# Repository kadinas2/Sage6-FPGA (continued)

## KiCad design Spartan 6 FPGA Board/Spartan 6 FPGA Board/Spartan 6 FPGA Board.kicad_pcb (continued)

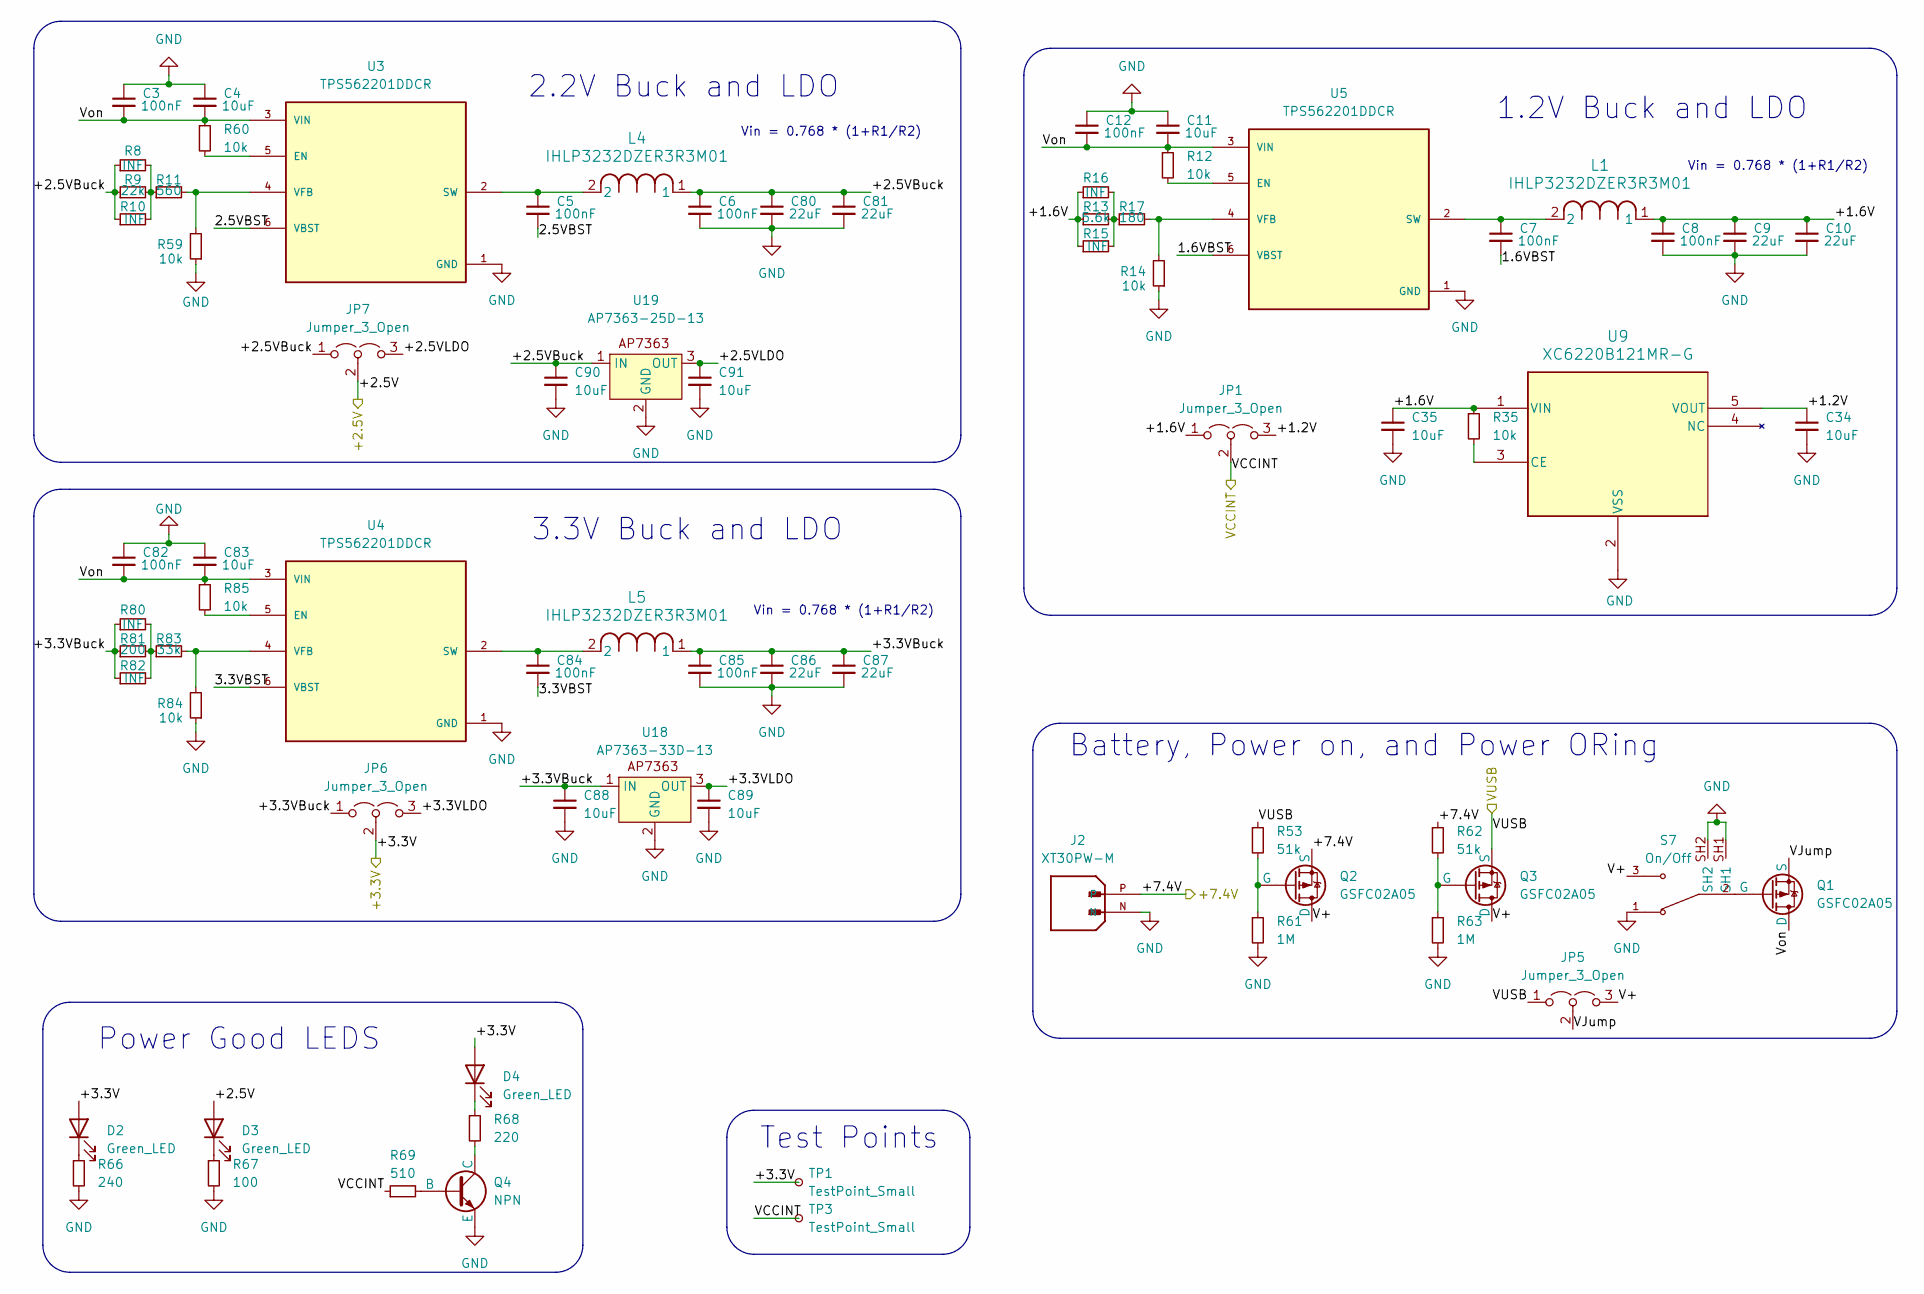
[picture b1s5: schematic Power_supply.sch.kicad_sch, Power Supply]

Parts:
C3, C5, C6, C7, C8, C12, C82, C84, C85: 100nF; C_0805_2012Metric_Pad1.18x1.45mm_HandSolder
C4, C11, C34, C35, C83, C88, C89, C90, C91: 10uF; C_0805_2012Metric_Pad1.18x1.45mm_HandSolder
C9, C10, C80, C81, C86, C87: 22uF; C_0805_2012Metric_Pad1.18x1.45mm_HandSolder
D2, D3, D4: Green_LED; LED_0805_2012Metric
J2: XT30PW-M; AMASS_XT30PW-M; PARTREV 1.2
JP1, JP5, JP6, JP7: Jumper_3_Open; PinHeader_1x03_P2.54mm_Vertical
L1, L4, L5: IHLP3232DZER3R3M01; IND_IHLP-3232DZ_VIS
Q1, Q2, Q3: GSFC02A05; SOT-23
Q4: NPN; SOT-23
R8, R10, R15, R16, R80, R82: INF; R_0805_2012Metric_Pad1.20x1.40mm_HandSolder
R9: 22k; R_0805_2012Metric_Pad1.20x1.40mm_HandSolder
R11: 560; R_0805_2012Metric_Pad1.20x1.40mm_HandSolder
R12, R14, R35, R59, R60, R84, R85: 10k; R_0805_2012Metric_Pad1.20x1.40mm_HandSolder
R13: 5.6k; R_0805_2012Metric_Pad1.20x1.40mm_HandSolder
R17: 180; R_0805_2012Metric_Pad1.20x1.40mm_HandSolder
R53, R62: 51k; R_0805_2012Metric_Pad1.20x1.40mm_HandSolder
R61, R63: 1M; R_0805_2012Metric_Pad1.20x1.40mm_HandSolder
R66: 240; R_0805_2012Metric_Pad1.20x1.40mm_HandSolder
R67: 100; R_0805_2012Metric_Pad1.20x1.40mm_HandSolder
R68: 220; R_0805_2012Metric_Pad1.20x1.40mm_HandSolder
R69: 510; R_0805_2012Metric_Pad1.20x1.40mm_HandSolder
R81: 200; R_0805_2012Metric_Pad1.20x1.40mm_HandSolder
R83: 33k; R_0805_2012Metric_Pad1.20x1.40mm_HandSolder
S7: On/Off; SW_SLW-835636-3A-RA-N-D; PARTREV 1.01
TP1, TP3: TestPoint_Small; TestPoint_Pad_D1.0mm
U3, U4, U5: TPS562201DDCR; SOT95P280X110-6N; PARTREV A
U9: XC6220B121MR-G; SOT-25_TOR
U18: AP7363-33D-13; TO-252-3_TabPin2
U19: AP7363-25D-13; TO-252-3_TabPin2

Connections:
/+2.5V: D3.2 (A), JP7.2 (C); also elsewhere on the board
/+3.3V: D2.2 (A), D4.2 (A), JP6.2 (C), TP1.1; also elsewhere on the board
/+7.4V: J2.P, Q2.3 (S), R62.1; also elsewhere on the board
/Power Supply/1.6VBST: C7.2, U5.6 (VBST)
/Power Supply/2.5VBST: C5.2, U3.6 (VBST)
/Power Supply/3.3VBST: C84.2, U4.6 (VBST)
/Power Supply/+1.2V: C34.1, JP1.3 (B), U9.5 (VOUT)
/Power Supply/+1.6V: C8.1, C9.1, C10.1, C35.1, JP1.1 (A), L1.1, R13.1, R15.1, R16.1, R35.1, U9.1 (VIN)
/Power Supply/+2.5VBuck: C6.1, C80.1, C81.1, C90.1, JP7.1 (A), L4.1, R8.1, R9.1, R10.1, U19.1 (IN)
/Power Supply/+2.5VLDO: C91.1, JP7.3 (B), U19.3 (OUT)
/Power Supply/+3.3VBuck: C85.1, C86.1, C87.1, C88.1, JP6.1 (A), L5.1, R80.1, R81.1, R82.1, U18.1 (IN)
/Power Supply/+3.3VLDO: C89.1, JP6.3 (B), U18.3 (OUT)
/Power Supply/V+: JP5.3 (B), Q2.1 (D), Q3.1 (D), S7.3
/Power Supply/VJump: JP5.2 (C), Q1.3 (S)
/Power Supply/Von: C3.2, C4.2, C11.2, C12.2, C82.2, C83.2, Q1.1 (D), R12.1, R60.1, R85.1, U3.3 (VIN), U4.3 (VIN), U5.3 (VIN)
/VCCINT: JP1.2 (C), R69.1, TP3.1; also elsewhere on the board
/VUSB: JP5.1 (A), Q3.3 (S), R53.1; also elsewhere on the board
GND: C3.1, C4.1, C6.2, C8.2, C9.2, C10.2, C11.1, C12.1, C34.2, C35.2, C80.2, C81.2, C82.1, C83.1, C85.2, C86.2, C87.2, C88.2, C89.2, C90.2, C91.2, J2.N, Q4.3 (E), R14.1, R59.1, R61.2, R63.2, R66.2, R67.2, R84.1, S7.1, S7.SH1, S7.SH2, U3.1 (GND), U4.1 (GND), U5.1 (GND), U9.2 (VSS), U18.2 (GND), U19.2 (GND); also elsewhere on the board
unnamed: D2.1 (K), R66.1
unnamed: D3.1 (K), R67.1
unnamed: D4.1 (K), R68.1
unnamed: Q1.2 (G), S7.2
unnamed: Q2.2 (G), R53.2, R61.1
unnamed: Q3.2 (G), R62.2, R63.1
unnamed: Q4.2 (B), R69.2
unnamed: Q4.1 (C), R68.2
unnamed: R8.2, R9.2, R10.2, R11.1
unnamed: R13.2, R15.2, R16.2, R17.1
unnamed: R80.2, R81.2, R82.2, R83.1
unnamed: R60.2, U3.5 (EN)
unnamed: C5.1, L4.2, U3.2 (SW)
unnamed: R11.2, R59.2, U3.4 (VFB)
unnamed: R85.2, U4.5 (EN)
unnamed: C84.1, L5.2, U4.2 (SW)
unnamed: R83.2, R84.2, U4.4 (VFB)
unnamed: R12.2, U5.5 (EN)
unnamed: C7.1, L1.2, U5.2 (SW)
unnamed: R14.2, R17.2, U5.4 (VFB)
unnamed: R35.2, U9.3 (CE)

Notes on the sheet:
1.2V Buck and LDO
3.3V Buck and LDO
Power Good LEDS
Test Points
2.2V Buck and LDO
Vin = 0.768 * (1+R1/R2)
Battery, Power on, and Power ORing

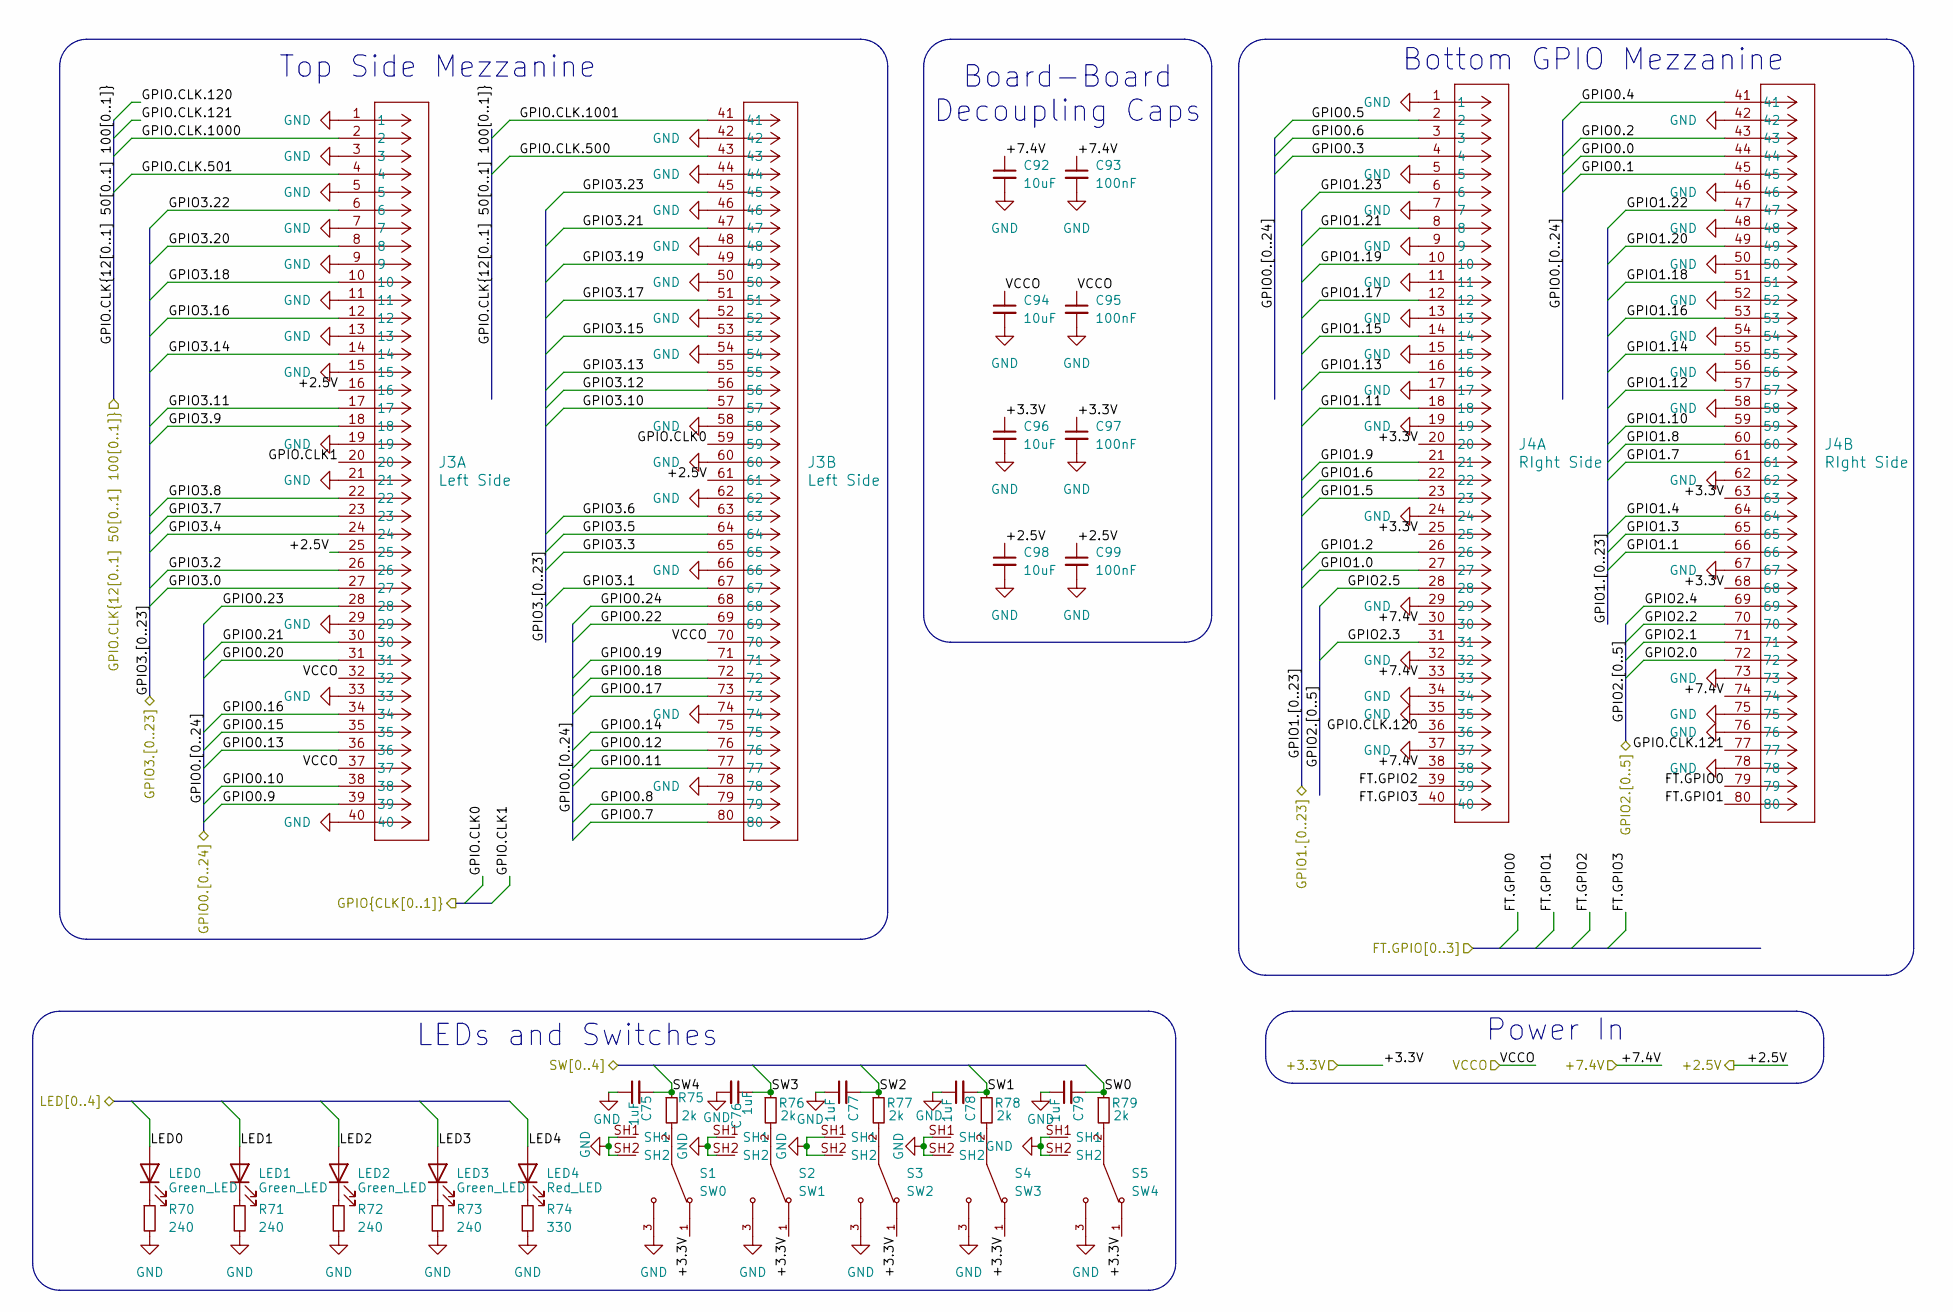
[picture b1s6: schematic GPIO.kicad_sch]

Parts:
C75, C76, C77, C78, C79: 1uF; C_0805_2012Metric_Pad1.18x1.45mm_HandSolder
C92, C94, C96, C98: 10uF; C_0805_2012Metric_Pad1.18x1.45mm_HandSolder
C93, C95, C97, C99: 100nF; C_0805_2012Metric_Pad1.18x1.45mm_HandSolder
J3: Left Side; CON80_2X40_MU_TX25_JAE
J4: RIght Side; CON80_2X40_MU_TX25_JAE
LED0, LED1, LED2, LED3: Green_LED; LED_0805_2012Metric
LED4: Red_LED; LED_0805_2012Metric
R70, R71, R72, R73: 240; R_0805_2012Metric_Pad1.20x1.40mm_HandSolder
R74: 330; R_0805_2012Metric_Pad1.20x1.40mm_HandSolder
R75, R76, R77, R78, R79: 2k; R_0805_2012Metric_Pad1.20x1.40mm_HandSolder
S1: SW0; SW_SLW-835636-3A-RA-N-D; PARTREV 1.01
S2: SW1; SW_SLW-835636-3A-RA-N-D; PARTREV 1.01
S3: SW2; SW_SLW-835636-3A-RA-N-D; PARTREV 1.01
S4: SW3; SW_SLW-835636-3A-RA-N-D; PARTREV 1.01
S5: SW4; SW_SLW-835636-3A-RA-N-D; PARTREV 1.01

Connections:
/+2.5V: C98.1, C99.1, J3.16, J3.25, J3.61; also elsewhere on the board
/+3.3V: C96.1, C97.1, J4.20, J4.25, J4.63, J4.68, S1.1, S2.1, S3.1, S4.1, S5.1; also elsewhere on the board
/+7.4V: C92.1, C93.1, J4.30, J4.33, J4.38, J4.74; also elsewhere on the board
/FT.GPIO0: J4.79; also elsewhere on the board
/FT.GPIO1: J4.80; also elsewhere on the board
/FT.GPIO2: J4.39; also elsewhere on the board
/FT.GPIO3: J4.40; also elsewhere on the board
/GPIO0.0: J4.44; also elsewhere on the board
/GPIO0.1: J4.45; also elsewhere on the board
/GPIO0.2: J4.43; also elsewhere on the board
/GPIO0.3: J4.4; also elsewhere on the board
/GPIO0.4: J4.41; also elsewhere on the board
/GPIO0.5: J4.2; also elsewhere on the board
/GPIO0.6: J4.3; also elsewhere on the board
/GPIO0.7: J3.80; also elsewhere on the board
/GPIO0.8: J3.79; also elsewhere on the board
/GPIO0.9: J3.39; also elsewhere on the board
/GPIO0.10: J3.38; also elsewhere on the board
/GPIO0.11: J3.77; also elsewhere on the board
/GPIO0.12: J3.76; also elsewhere on the board
/GPIO0.13: J3.36; also elsewhere on the board
/GPIO0.14: J3.75; also elsewhere on the board
/GPIO0.15: J3.35; also elsewhere on the board
/GPIO0.16: J3.34; also elsewhere on the board
/GPIO0.17: J3.73; also elsewhere on the board
/GPIO0.18: J3.72; also elsewhere on the board
/GPIO0.19: J3.71; also elsewhere on the board
/GPIO0.20: J3.31; also elsewhere on the board
/GPIO0.21: J3.30; also elsewhere on the board
/GPIO0.22: J3.69; also elsewhere on the board
/GPIO0.23: J3.28; also elsewhere on the board
/GPIO0.24: J3.68; also elsewhere on the board
/GPIO1.0: J4.27; also elsewhere on the board
/GPIO1.1: J4.66; also elsewhere on the board
/GPIO1.2: J4.26; also elsewhere on the board
/GPIO1.3: J4.65; also elsewhere on the board
/GPIO1.4: J4.64; also elsewhere on the board
/GPIO1.5: J4.23; also elsewhere on the board
/GPIO1.6: J4.22; also elsewhere on the board
/GPIO1.7: J4.61; also elsewhere on the board
/GPIO1.8: J4.60; also elsewhere on the board
/GPIO1.9: J4.21; also elsewhere on the board
/GPIO1.10: J4.59; also elsewhere on the board
/GPIO1.11: J4.18; also elsewhere on the board
/GPIO1.12: J4.57; also elsewhere on the board
/GPIO1.13: J4.16; also elsewhere on the board
/GPIO1.14: J4.55; also elsewhere on the board
/GPIO1.15: J4.14; also elsewhere on the board
/GPIO1.16: J4.53; also elsewhere on the board
/GPIO1.17: J4.12; also elsewhere on the board
/GPIO1.18: J4.51; also elsewhere on the board
/GPIO1.19: J4.10; also elsewhere on the board
/GPIO1.20: J4.49; also elsewhere on the board
/GPIO1.21: J4.8; also elsewhere on the board
/GPIO1.22: J4.47; also elsewhere on the board
/GPIO1.23: J4.6; also elsewhere on the board
/GPIO2.0: J4.72; also elsewhere on the board
/GPIO2.1: J4.71; also elsewhere on the board
/GPIO2.2: J4.70; also elsewhere on the board
/GPIO2.3: J4.31; also elsewhere on the board
/GPIO2.4: J4.69; also elsewhere on the board
/GPIO2.5: J4.28; also elsewhere on the board
/GPIO3.0: J3.27; also elsewhere on the board
/GPIO3.1: J3.67; also elsewhere on the board
/GPIO3.2: J3.26; also elsewhere on the board
/GPIO3.3: J3.65; also elsewhere on the board
/GPIO3.4: J3.24; also elsewhere on the board
/GPIO3.5: J3.64; also elsewhere on the board
/GPIO3.6: J3.63; also elsewhere on the board
/GPIO3.7: J3.23; also elsewhere on the board
/GPIO3.8: J3.22; also elsewhere on the board
/GPIO3.9: J3.18; also elsewhere on the board
/GPIO3.10: J3.57; also elsewhere on the board
/GPIO3.11: J3.17; also elsewhere on the board
/GPIO3.12: J3.56; also elsewhere on the board
/GPIO3.13: J3.55; also elsewhere on the board
/GPIO3.14: J3.14; also elsewhere on the board
/GPIO3.15: J3.53; also elsewhere on the board
/GPIO3.16: J3.12; also elsewhere on the board
/GPIO3.17: J3.51; also elsewhere on the board
/GPIO3.18: J3.10; also elsewhere on the board
/GPIO3.19: J3.49; also elsewhere on the board
/GPIO3.20: J3.8; also elsewhere on the board
/GPIO3.21: J3.47; also elsewhere on the board
/GPIO3.22: J3.6; also elsewhere on the board
/GPIO3.23: J3.45; also elsewhere on the board
/GPIO.CLK0: J3.59; also elsewhere on the board
/GPIO.CLK1: J3.20; also elsewhere on the board
/GPIO.CLK.120: J4.36; also elsewhere on the board
/GPIO.CLK.121: J4.77; also elsewhere on the board
/GPIO.CLK.500: J3.43; also elsewhere on the board
/GPIO.CLK.501: J3.4; also elsewhere on the board
/GPIO.CLK.1000: J3.2; also elsewhere on the board
/GPIO.CLK.1001: J3.41; also elsewhere on the board
/LED0: LED0.2 (A); also elsewhere on the board
/LED1: LED1.2 (A); also elsewhere on the board
/LED2: LED2.2 (A); also elsewhere on the board
/LED3: LED3.2 (A); also elsewhere on the board
/LED4: LED4.2 (A); also elsewhere on the board
/SW0: C79.2, R79.1; also elsewhere on the board
/SW1: C78.2, R78.1; also elsewhere on the board
/SW2: C77.2, R77.1; also elsewhere on the board
/SW3: C76.1, R76.1; also elsewhere on the board
/SW4: C75.2, R75.1; also elsewhere on the board
/VCCO: C94.1, C95.1, J3.32, J3.37, J3.70; also elsewhere on the board
GND: C75.1, C76.2, C77.1, C78.1, C79.1, C92.2, C93.2, C94.2, C95.2, C96.2, C97.2, C98.2, C99.2, J3.1, J3.3, J3.5, J3.7, J3.9, J3.11, J3.13, J3.15, J3.19, J3.21, J3.29, J3.33, J3.40, J3.42, J3.44, J3.46, J3.48, J3.50, J3.52, J3.54, J3.58, J3.60, J3.62, J3.66, J3.74, J3.78, J4.1, J4.5, J4.7, J4.9, J4.11, J4.13, J4.15, J4.17, J4.19, J4.24, J4.29, J4.32, J4.34, J4.35, J4.37, J4.42, J4.46, J4.48, J4.50, J4.52, J4.54, J4.56, J4.58, J4.62, J4.67, J4.73, J4.75, J4.76, J4.78, R70.2, R71.2, R72.2, R73.2, R74.2, S1.3, S1.SH1, S1.SH2, S2.3, S2.SH1, S2.SH2, S3.3, S3.SH1, S3.SH2, S4.3, S4.SH1, S4.SH2, S5.3, S5.SH1, S5.SH2; also elsewhere on the board
unnamed: LED0.1 (K), R70.1
unnamed: LED1.1 (K), R71.1
unnamed: LED2.1 (K), R72.1
unnamed: LED3.1 (K), R73.1
unnamed: LED4.1 (K), R74.1
unnamed: R75.2, S1.2
unnamed: R76.2, S2.2
unnamed: R77.2, S3.2
unnamed: R78.2, S4.2
unnamed: R79.2, S5.2

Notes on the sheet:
Top Side Mezzanine
Bottom GPIO Mezzanine
Board-Board Decoupling Caps
LEDs and Switches
Power In

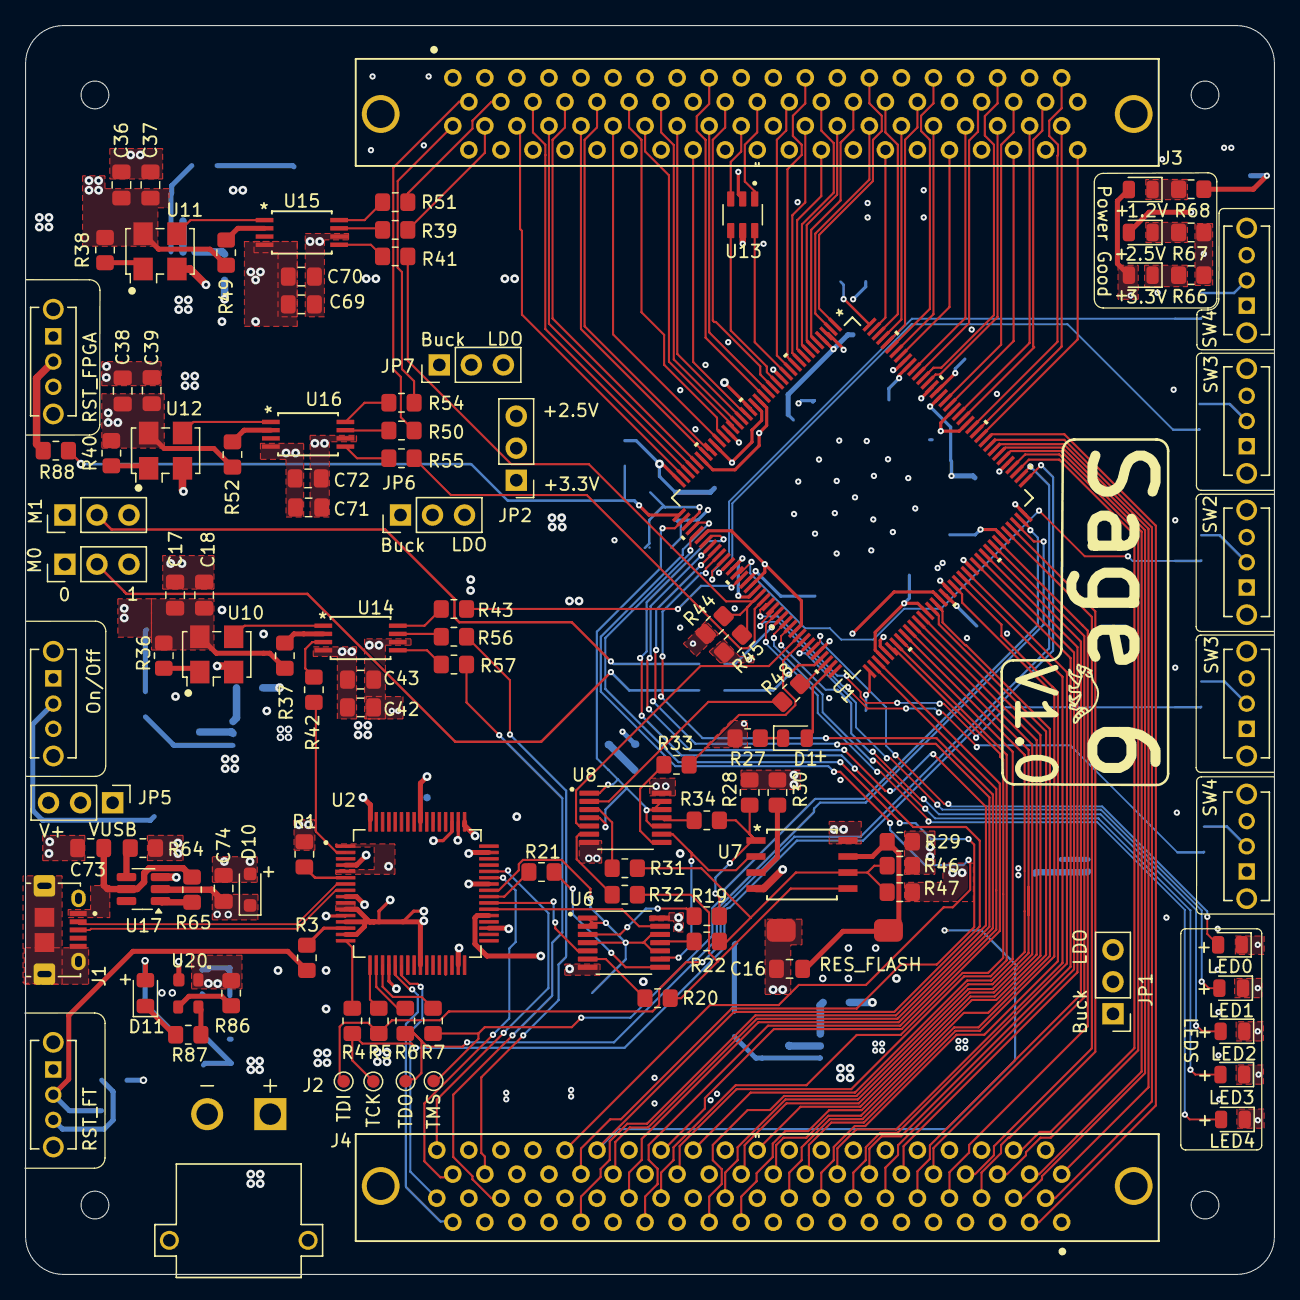
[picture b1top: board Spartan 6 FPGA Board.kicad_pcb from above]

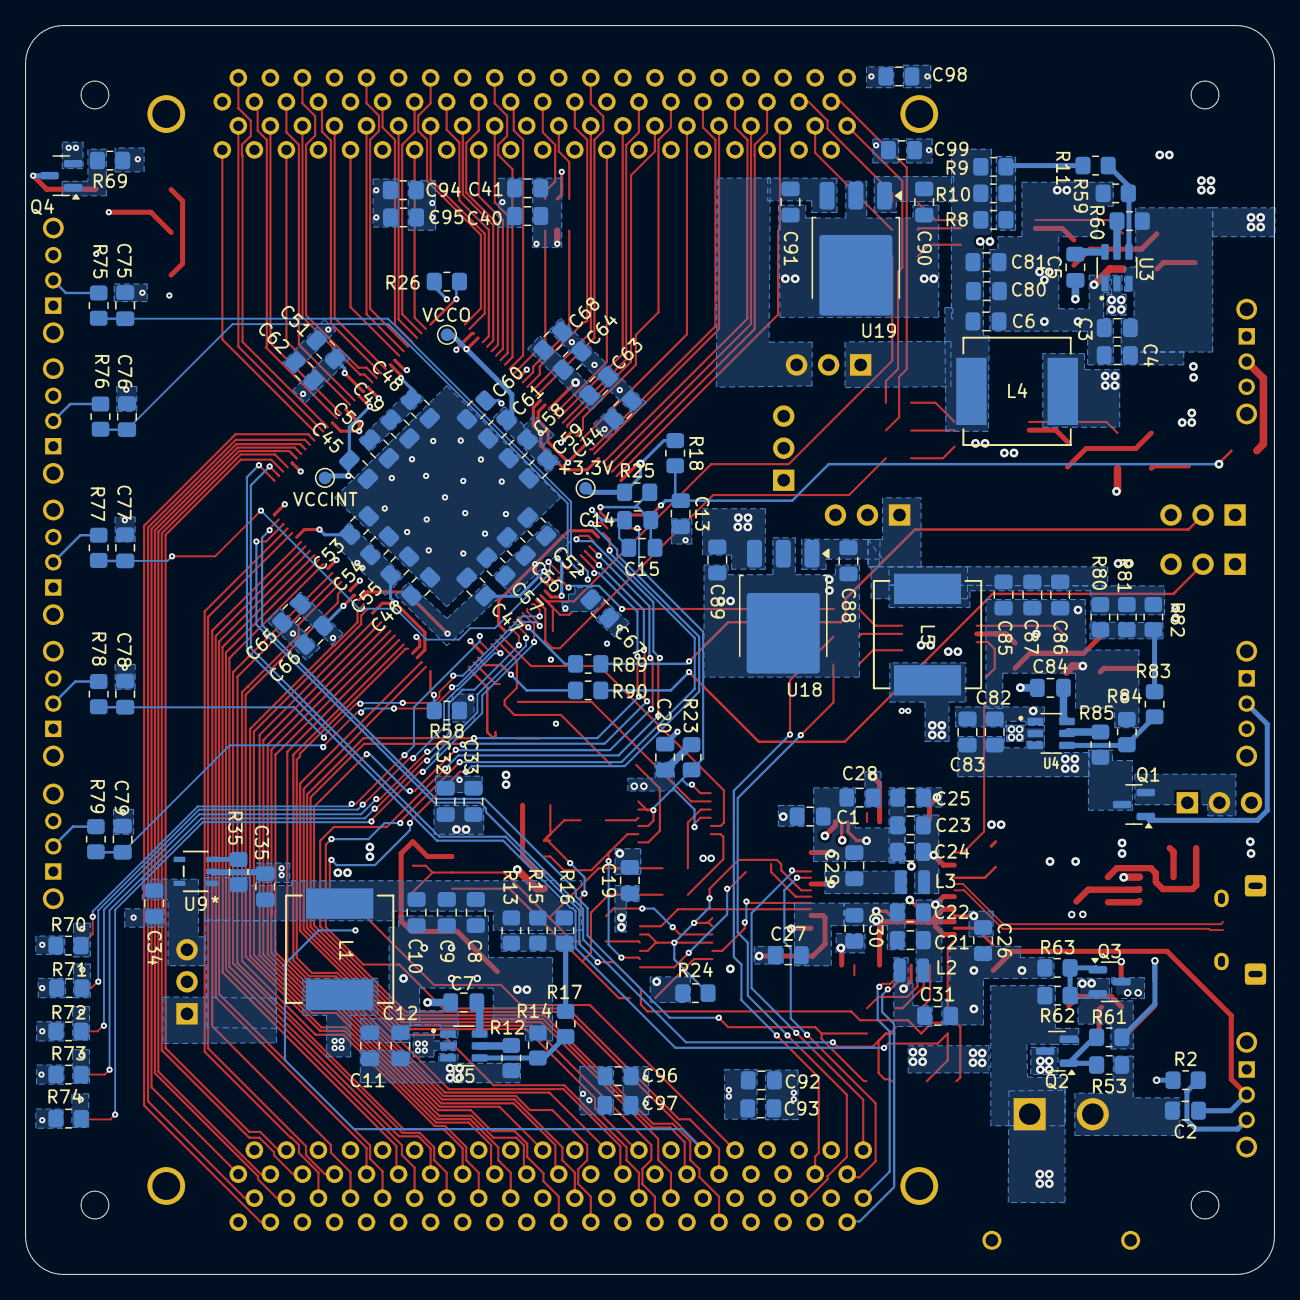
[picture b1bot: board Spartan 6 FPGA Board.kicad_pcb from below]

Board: 4 copper layers, 99.0 x 99.0 mm, 260 parts (145 on the bottom side), 233 nets.

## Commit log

2025-08-27 Add files via upload
    Updated files with new libraries
